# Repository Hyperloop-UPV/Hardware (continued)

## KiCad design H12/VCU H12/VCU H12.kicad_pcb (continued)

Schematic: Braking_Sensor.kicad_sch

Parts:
C108, C109, C110, C111, C112, C113: 0.1uF; CAP 0603_1608
C114: 1.6u; C_0603_1608Metric
C115: 0.1u; C_0603_1608Metric
IC7, IC12: SN74LVC86AD; SOIC127P600X175-14N; Manufacturer_Part_Number SN74LVC86AD; Mouser Part Number 595-SN74LVC86AD
IC8, IC9, IC10, IC11: SN74LVC08AD; SOIC127P600X175-14N; Manufacturer_Part_Number SN74LVC08AD; Mouser Part Number 595-SN74LVC08AD
IC13: SN74LVC1G17DBVR; Manufacturer_Part_Number SN74LVC1G17DBVR; Mouser Part Number 595-SN74LVC1G17DBVR
J27: 206832-0401; 206832-0401-Footprint-1; MAX VOLTAGE 600V AC (RMS)/DC
R150: 670; R_0603_1608Metric
R151, R152: 0 Ohms; RES 0603_1608; RATINGS AEC-Q200; TOLERANCE Jumper; PART NUMBER TLRZ1JTTD
TP42, TP43, TP44, TP45, TP46, TP47, TP48, TP49, TP50, TP51, TP52, TP53, TP54, TP55, TP56, TP57, TP58, TP59, TP60, TP61, TP62, TP63, TP64, TP65, TP66, TP67, TP68, TP69, TP70, TP71, TP72, TP73, TP74, TP75, TP77, TP78, TP79, TP80: Test point 1.2mm; Test point 1.2mm-Footprint-1

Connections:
+3V3: C108.1, C109.1, C110.1, C111.1, C112.1, C113.1, C115.1, IC7.14 (VCC), IC8.14 (VCC), IC9.14 (VCC), IC10.14 (VCC), IC11.14 (VCC), IC12.14 (VCC), IC13.5 (VCC); also elsewhere on the board
/Braking_Sensor/BRAKE_FAULT: IC11.12 (4A), IC13.4 (Y); also elsewhere on the board
/Braking_Sensor/BRAKE_RESET: IC9.9 (3A), R151.1, TP71.1 (*_1); also elsewhere on the board
/Braking_Sensor/GD_Reset_bypass: J27.3, J27.4, R151.2, R152.2, TP70.1 (*_1)
/Braking_Sensor/SENSOR_1_NC_OUT: IC7.2 (1B), TP43.1 (*_1); also elsewhere on the board
/Braking_Sensor/SENSOR_1_NO_OUT: IC7.1 (1A), IC10.1 (1A), TP42.1 (*_1); also elsewhere on the board
/Braking_Sensor/SENSOR_2_NC_OUT: IC7.5 (2B), TP47.1 (*_1); also elsewhere on the board
/Braking_Sensor/SENSOR_2_NO_OUT: IC7.4 (2A), IC10.2 (1B), TP46.1 (*_1); also elsewhere on the board
/Braking_Sensor/SENSOR_3_NC_OUT: IC7.10 (3B), TP49.1 (*_1); also elsewhere on the board
/Braking_Sensor/SENSOR_3_NO_OUT: IC7.9 (3A), IC10.4 (2A), TP48.1 (*_1); also elsewhere on the board
/Braking_Sensor/SENSOR_4_NC_OUT: IC7.13 (4B), TP54.1 (*_1); also elsewhere on the board
/Braking_Sensor/SENSOR_4_NO_OUT: IC7.12 (4A), IC10.5 (2B), TP53.1 (*_1); also elsewhere on the board
/Braking_Sensor/SENSOR_5_NC_OUT: IC12.2 (1B), TP57.1 (*_1); also elsewhere on the board
/Braking_Sensor/SENSOR_5_NO_OUT: IC10.9 (3A), IC12.1 (1A), TP55.1 (*_1); also elsewhere on the board
/Braking_Sensor/SENSOR_6_NC_OUT: IC12.5 (2B), TP62.1 (*_1); also elsewhere on the board
/Braking_Sensor/SENSOR_6_NO_OUT: IC10.10 (3B), IC12.4 (2A), TP59.1 (*_1); also elsewhere on the board
/Braking_Sensor/SENSOR_7_NC_OUT: IC12.10 (3B), TP66.1 (*_1); also elsewhere on the board
/Braking_Sensor/SENSOR_7_NO_OUT: IC10.12 (4A), IC12.9 (3A), TP64.1 (*_1); also elsewhere on the board
/Braking_Sensor/SENSOR_8_NC_OUT: IC12.13 (4B), TP69.1 (*_1); also elsewhere on the board
/Braking_Sensor/SENSOR_8_NO_OUT: IC10.13 (4B), IC12.12 (4A), TP67.1 (*_1); also elsewhere on the board
/MCU/RELEASED: IC9.10 (3B), IC11.11 (4Y), TP72.1 (*_1); also elsewhere on the board
GND: C108.2, C109.2, C110.2, C111.2, C112.2, C113.2, C114.2, C115.2, IC7.7 (GND), IC8.7 (GND), IC9.7 (GND), IC10.7 (GND), IC11.7 (GND), IC12.7 (GND), IC13.3 (GND), J27.1, J27.2; also elsewhere on the board
unnamed: IC7.3 (1Y), IC8.1 (1A), TP44.1 (*_1)
unnamed: IC7.6 (2Y), IC8.2 (1B), TP45.1 (*_1)
unnamed: IC7.8 (3Y), IC8.4 (2A), TP51.1 (*_1)
unnamed: IC7.11 (4Y), IC8.5 (2B), TP52.1 (*_1)
unnamed: IC8.3 (1Y), IC9.1 (1A)
unnamed: IC8.6 (2Y), IC9.2 (1B)
unnamed: IC8.8 (3Y), IC9.4 (2A), TP58.1 (*_1)
unnamed: IC8.11 (4Y), IC9.5 (2B), TP63.1 (*_1)
unnamed: IC9.3 (1Y), IC9.12 (4A), TP50.1 (*_1)
unnamed: IC9.6 (2Y), IC9.13 (4B), TP60.1 (*_1)
unnamed: IC9.8 (3Y), R152.1
unnamed: IC9.11 (4Y), R150.1
unnamed: IC10.3 (1Y), IC11.1 (1A), TP73.1 (*_1)
unnamed: IC10.6 (2Y), IC11.2 (1B), TP75.1 (*_1)
unnamed: IC10.8 (3Y), IC11.4 (2A), TP78.1 (*_1)
unnamed: IC10.11 (4Y), IC11.5 (2B), TP80.1 (*_1)
unnamed: IC11.3 (1Y), IC11.9 (3A), TP74.1 (*_1)
unnamed: IC11.6 (2Y), IC11.10 (3B), TP79.1 (*_1)
unnamed: IC11.8 (3Y), IC11.13 (4B), TP77.1 (*_1)
unnamed: IC8.9 (3A), IC12.3 (1Y), TP56.1 (*_1)
unnamed: IC8.10 (3B), IC12.6 (2Y), TP61.1 (*_1)
unnamed: IC8.12 (4A), IC12.8 (3Y), TP65.1 (*_1)
unnamed: IC8.13 (4B), IC12.11 (4Y), TP68.1 (*_1)
unnamed: C114.1, IC13.2 (A), R150.2

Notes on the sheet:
XOR
Limit switch logic
AND
When Brake Disengaged, RELEASED = 1
1ms delay
NEVER solder both 0 ohm resistors at the same time
If BRAKE_FAULT = 0 something goes wrong
We need 3V3 in the gate driver RESET pin to enable PWMs
Connector to PPU and LPU Gate Drivers
The RESET pin in the gate driver works like a ENABLE

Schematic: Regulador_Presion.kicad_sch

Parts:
C116: 0.1 µF; CAP 0603_1608; TOLERANCE ±10%; VOLTAGE - RATED 50V; PART NUMBER C0603X104K050T
C117: 1 µF; CAP 1206_3216 - 0.8MM; RATINGS AEC-Q200; TOLERANCE ±10%; PART NUMBER C1206C105K5RACAUTO
C118, C119: 0.1 µF; CAP 0603_1608; RATINGS AEC-Q200; TOLERANCE ±10%; PART NUMBER CGA3E2X7R1H104K080AE
F1: 0308.500UR; New footprint 1; CURRENT RATING 500mA
J28: 206832-0401; 206832-0401-Footprint-1; MAX VOLTAGE 600V AC (RMS)/DC
R153: 100 kOhms; RES 0603_1608; TOLERANCE ±1%; PART NUMBER CRCW0603100KFKEAC
R154: 0 Ohm; FP-CRG0603-IPC_C; VOLTAGE RATING 50V; POWER RATING 100mW
R155: 5.1kOhms; YAGEO RES 0603_1608; TOLERANCE ±1%; PART NUMBER RT0603FRE0710KL
R156: 10kOhms; YAGEO RES 0603_1608; TOLERANCE ±0.1%; PART NUMBER RT0603BRD074K7L
R157: 39 kOhms; YAGEO RES 0603_1608; TOLERANCE ±1%; PART NUMBER RT0603FRE0710KL
R158: 1kOhms; RESC1608X55X25LL10T15; PART NUMBER RC0603JR-101KL
R159: 68 kOhms; RES 0603_1608; RATINGS AEC-Q200; TOLERANCE ±1%; PART NUMBER RMCF0603FT6K80
T4, T5: Test point 1.2mm; Test point 1.2mm-Footprint-1
U11: MCP6022-E/SN; SOIC-SN8_N; VOLTAGE GAIN-MIN 31620; SUPPLY VOLTAGE-NOM (VSU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 5V

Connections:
+5V: C116.2, C117.1, U11.8 (VDD); also elsewhere on the board
/MCU/REGULATOR_IN: R153.1; also elsewhere on the board
/MCU/REGULATOR_OUT: C119.2, R158.2, T5.1 (*_1); also elsewhere on the board
/Regulador_Presion/3.18V: R157.1, R159.2, U11.5 (VINB+)
/Regulador_Presion/REG_IN: J28.4, R154.2, T4.1 (*_1)
/Regulador_Presion/REG_OUT: J28.3, R157.2
/Regulador_Presion/V_SUPPLY_1: F1.2, J28.1
GND: C116.1, C117.2, C118.1, C119.1, J28.2, R156.1, R159.1, U11.4 (VSS); also elsewhere on the board
unnamed: C118.2, R153.2, U11.3 (VINA+)
unnamed: R155.2, R156.2, U11.2 (VINA-)
unnamed: R154.1, R155.1, U11.1 (VOUTA)
unnamed: R158.1, U11.6 (VINB-), U11.7 (VOUTB)
VBAT: F1.1; also elsewhere on the board

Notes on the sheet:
Conector
Regulator OUT
Regulator IN
Supply
Resistencia de 0 Ohms para poder ajustar la resistencia interna del regulador. La Rinterna es de 250 ohms, a 5V max = 20mA.
Señal de 0V to 3.3V (0.005 to 0.9 MPa)
Gain de 1.51 (para pasar de 3.3V a 5V max)
1V to 5V (0.005 to 0.9MPa)
0.636V to 3.18V (0.005 to 0.9MPa)
Pin Out: Brown = Vdc (24V) Blue = GND White = Analog Signal IN, sink type (4mA to 20mA) Black = Analog Signal Monitoring (1V to 5V) Rango de presion (0.005 to 0.9 MPa)

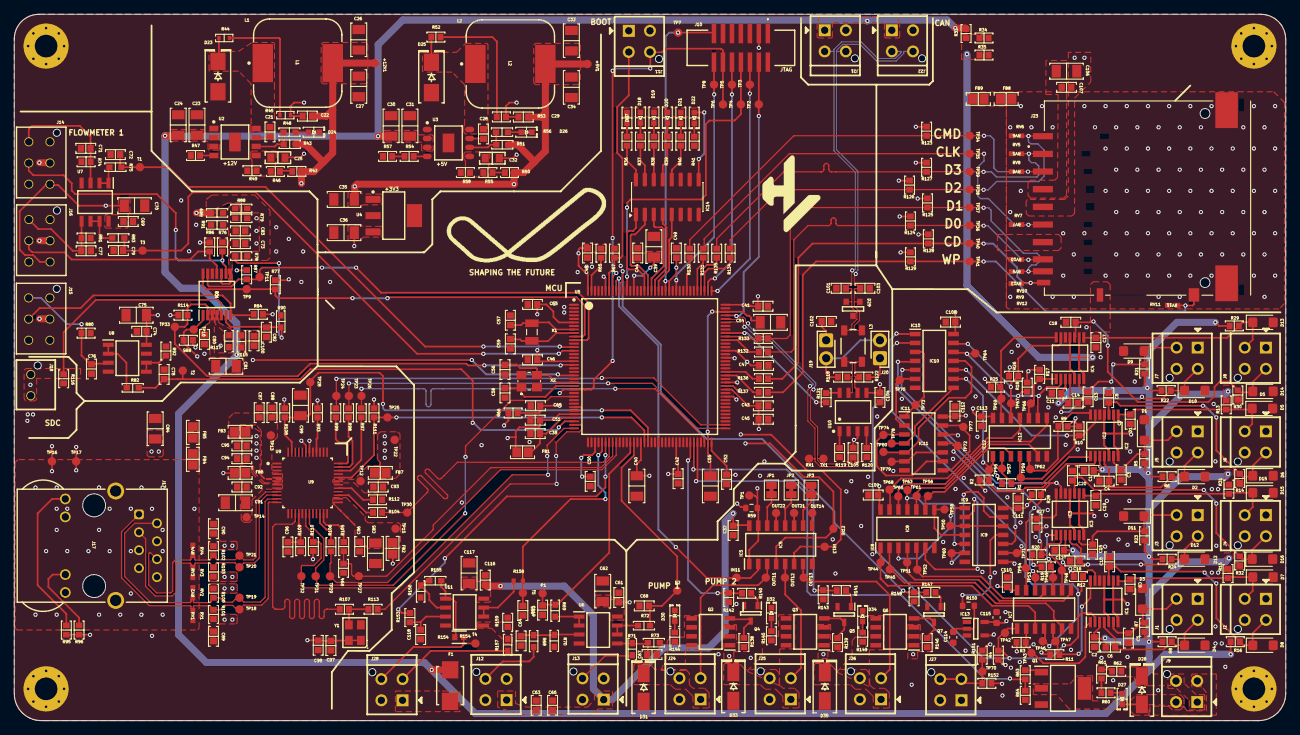
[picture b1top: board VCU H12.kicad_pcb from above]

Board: 6 copper layers, 180.0 x 100.0 mm, 506 parts (0 on the bottom side), 258 nets.

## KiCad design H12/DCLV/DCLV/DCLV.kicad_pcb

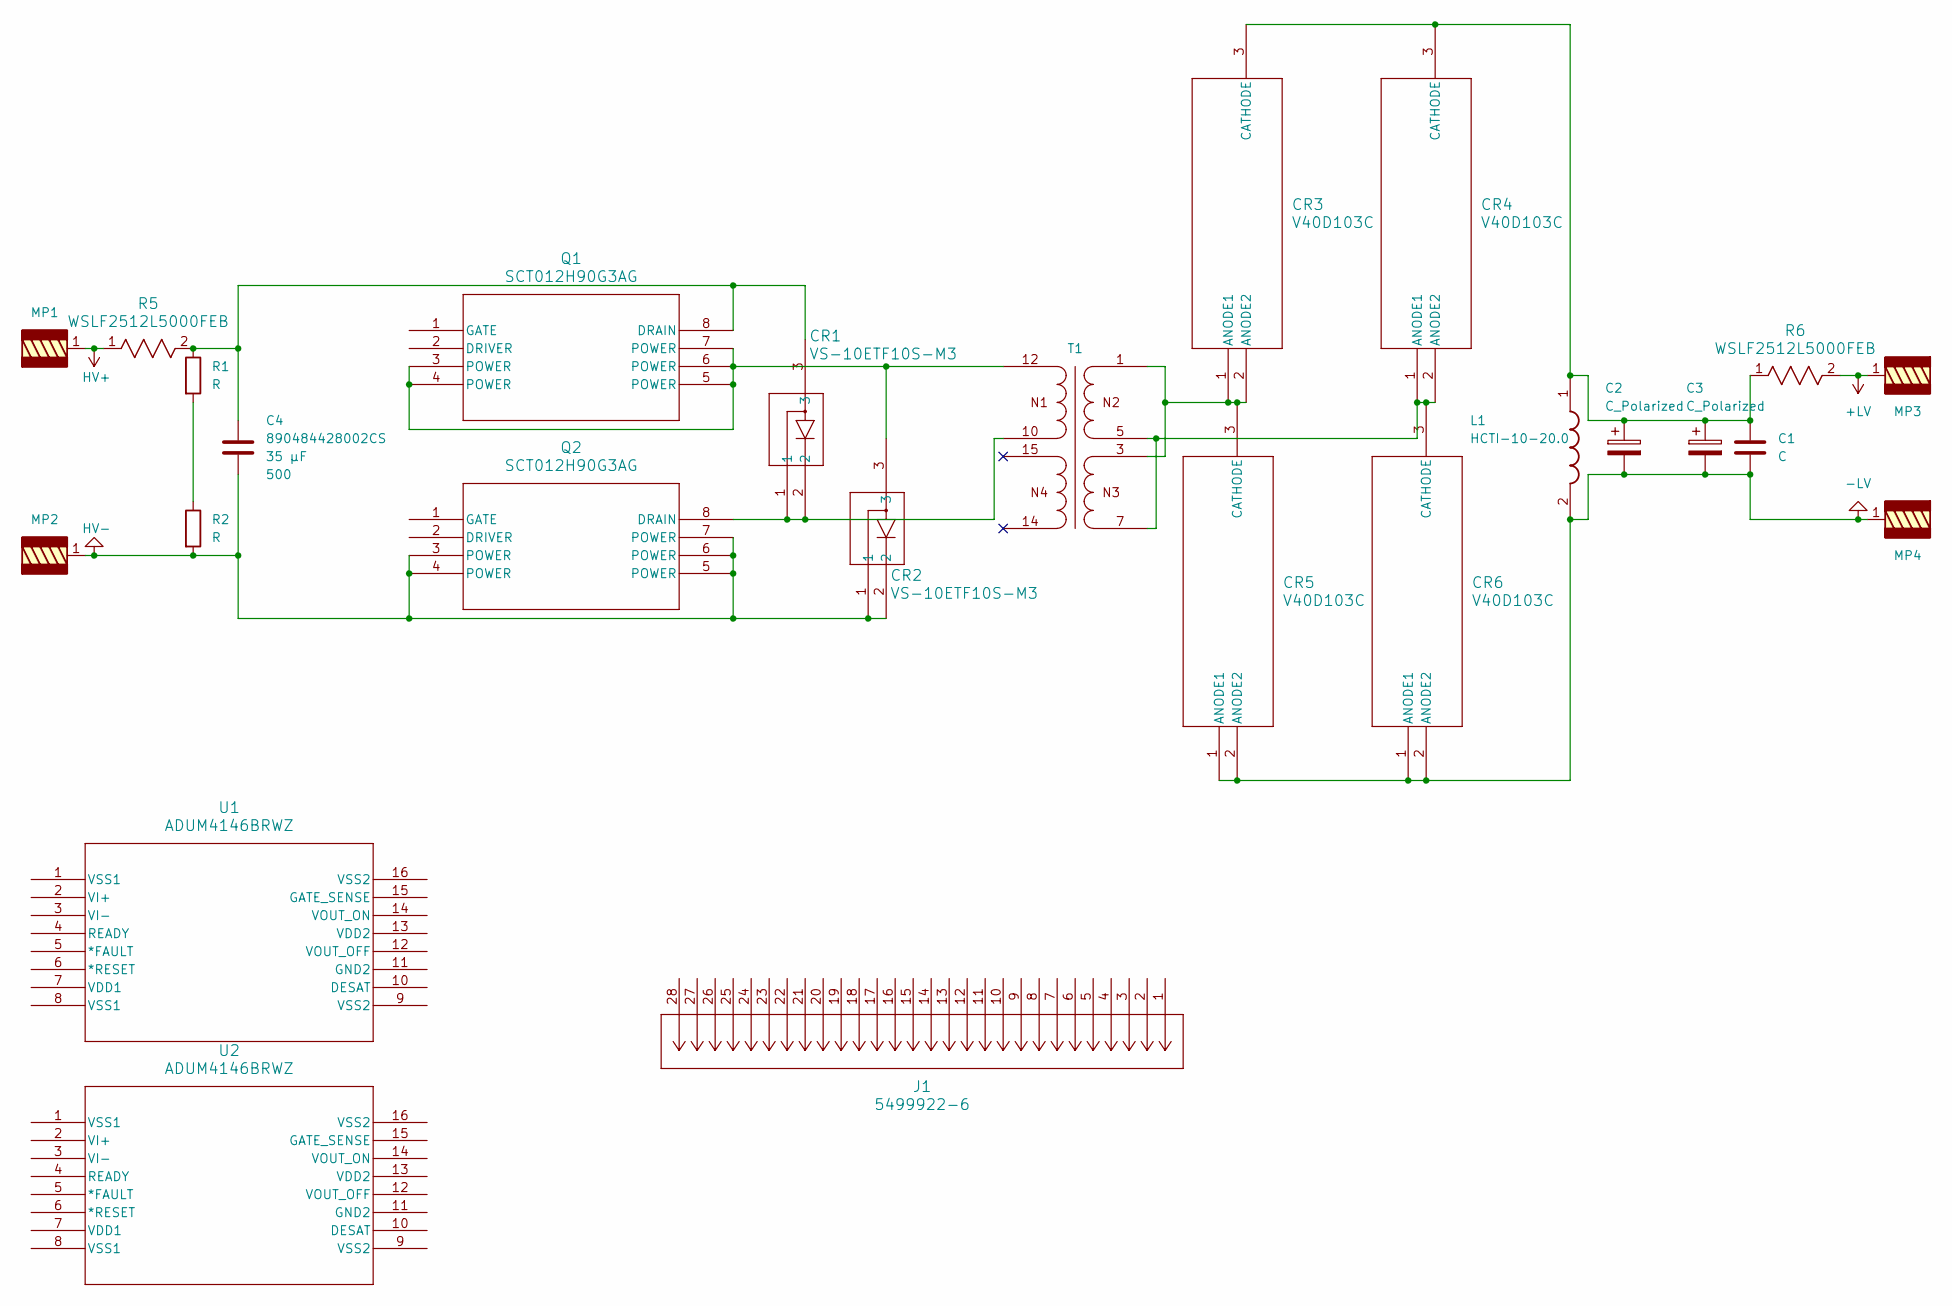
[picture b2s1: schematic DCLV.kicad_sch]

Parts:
C1: C; C_0805_2012Metric_Pad1.18x1.45mm_HandSolder
C2, C3: C_Polarized; CP_Radial_D18.0mm_P7.50mm
C4: L42W24H36_890484428002CS; C_Wurth_WCAP-FTDB-L42W24H36; Voltage 500; Part Number 890484428002CS
CR1, CR2: VS-10ETF10S-M3; TO-263AB_VIS
CR3, CR4, CR5, CR6: V40D103C; SDO_TO263AC_VIS
J1: 5499922-6; CON26_2X13_SHM_TEC
L1: HCTI-10-20.0; HCTI10200; Mouser Part Number 530-HCTI-10-20.0
MP1, MP2, MP3, MP4: 7460408; MP_Wurth_WP-BUCF_7460408; Part Number 7460408
Q1, Q2: SCT012H90G3AG; H2PAK-7_STM
R1, R2: R; R_1206_3216Metric_Pad1.30x1.75mm_HandSolder
R5, R6: WSLF2512L5000FEB; RES_WSLF2512_VIS
T1: ETD44_760895741; T_Wurth_WE-LLCR-ETD44; Part Number 760895741
U1, U2: ADUM4146BRWZ; RW-16_ADI

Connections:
HV+: MP1.1 (1_1), R5.1
HV-: C4.2, CR2.1, CR2.2, MP2.1 (1_1), Q2.3 (POWER), Q2.4 (POWER), Q2.5 (POWER), Q2.6 (POWER), Q2.7 (POWER), R2.2
LV+: MP3.1 (1_1), R6.2
LV-: C1.2, C2.2, C3.2, CR5.1 (ANODE1), CR5.2 (ANODE2), CR6.1 (ANODE1), CR6.2 (ANODE2), L1.2, MP4.1 (1_1)
unnamed: CR2.3, Q1.3 (POWER), Q1.4 (POWER), Q1.5 (POWER), Q1.6 (POWER), Q1.7 (POWER), T1.12
unnamed: CR3.1 (ANODE1), CR3.2 (ANODE2), CR5.3 (CATHODE), T1.1, T1.2, T1.3, T1.4
unnamed: C1.1, C2.1, C3.1, CR3.3 (CATHODE), CR4.3 (CATHODE), L1.1, R6.1
unnamed: CR4.1 (ANODE1), CR4.2 (ANODE2), CR6.3 (CATHODE), T1.5, T1.6, T1.7, T1.8
unnamed: C4.1, CR1.3, Q1.8 (DRAIN), R1.1, R5.2
unnamed: CR1.1, CR1.2, Q2.8 (DRAIN), T1.10
unnamed: R1.2, R2.1

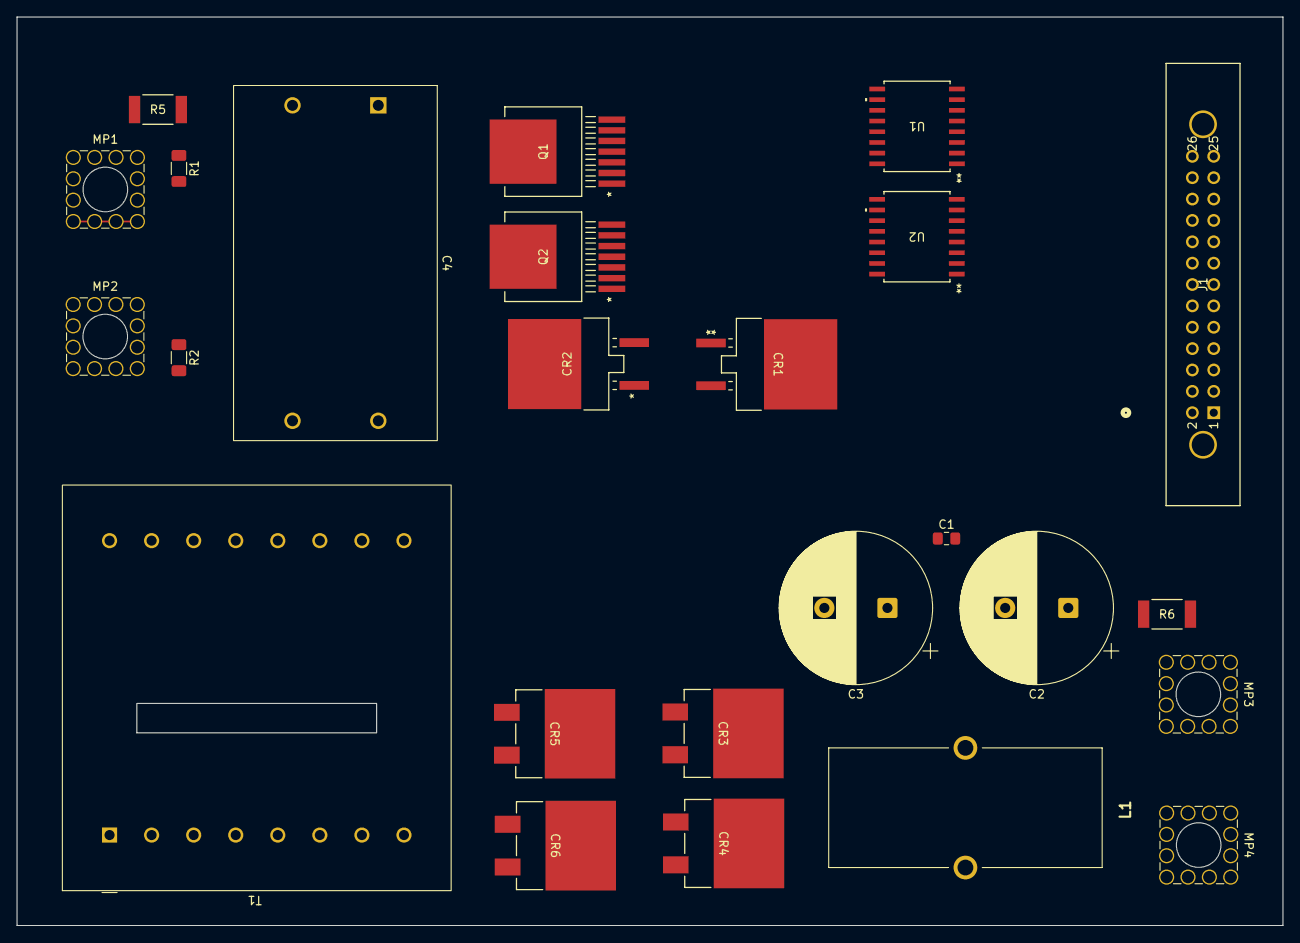
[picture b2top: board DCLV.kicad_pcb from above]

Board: 4 copper layers, 150.5 x 108.0 mm, 25 parts (0 on the bottom side), 11 nets.

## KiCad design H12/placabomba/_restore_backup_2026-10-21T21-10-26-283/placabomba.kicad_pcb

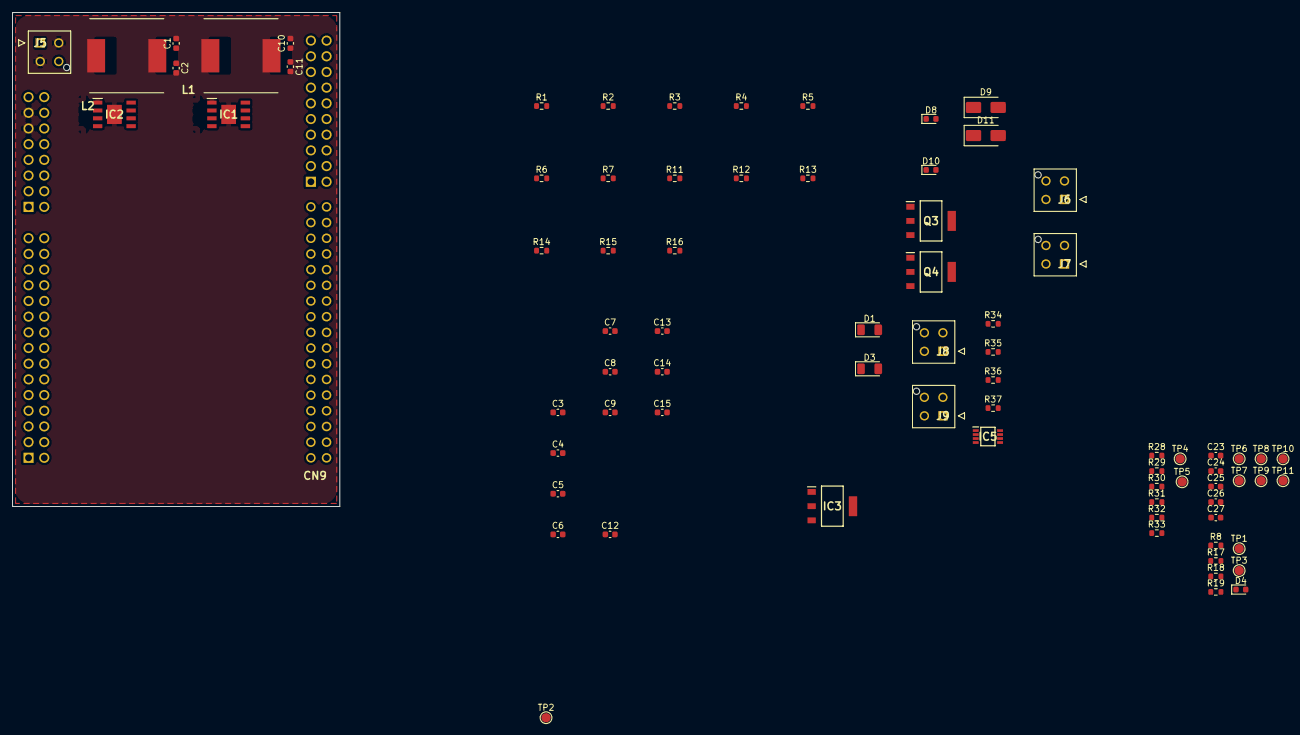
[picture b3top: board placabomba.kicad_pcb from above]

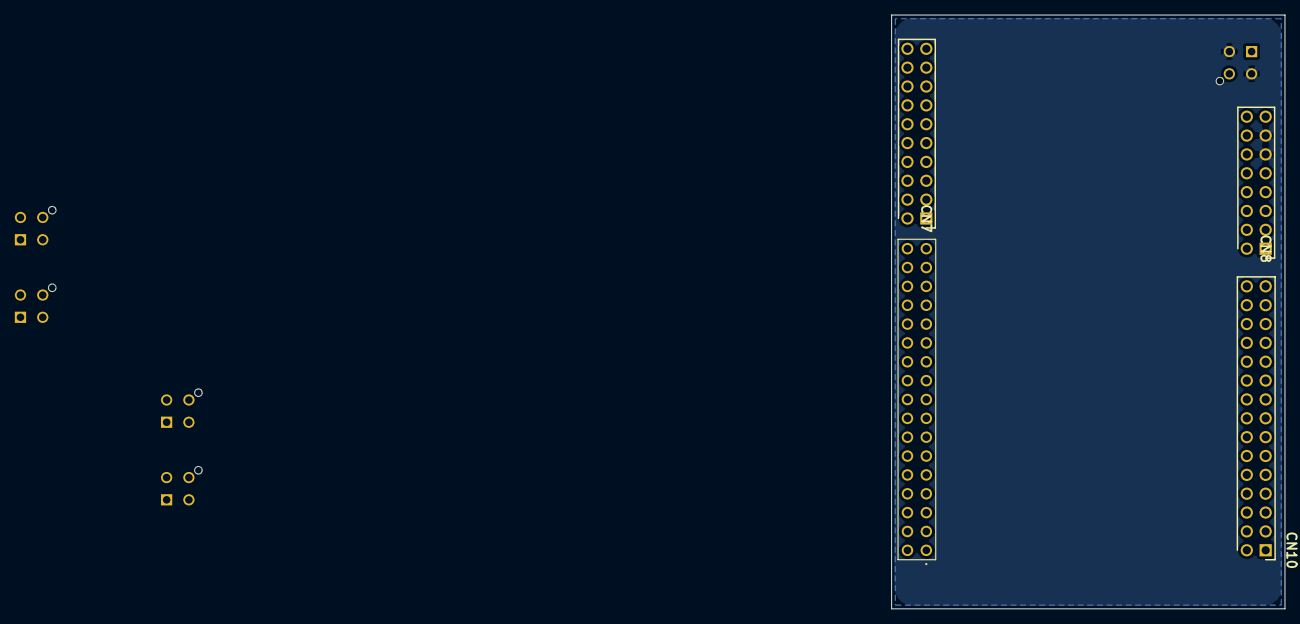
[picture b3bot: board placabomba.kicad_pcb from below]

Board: 2 copper layers, 53.0 x 80.0 mm, 82 parts (4 on the bottom side), 39 nets, no tracks yet.

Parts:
C1, C2, C10, C11: 2.2uF; C_0603_1608Metric
C3, C12, C23, C26, C27: 0.1uF; C_0603_1608Metric
C4: 56pF; C_0603_1608Metric
C5: 2200pF; C_0603_1608Metric
C6, C7, C15: 22uF; C_0603_1608Metric
C8, C9: 10uF; C_0603_1608Metric
C13: 47pF; C_0603_1608Metric
C14: 1200pF; C_0603_1608Metric
C24, C25: 100uF; C_0603_1608Metric
CN7: TSW-110-23-G-D; HDRV20W64P254_2X10_2540X495X838P
CN8: TSW-108-23-G-D; HDRV16W64P254_2X8_2032X495X838P
CN9: TSW-115-23-G-D; TSW-117-XX-YY-D
CN10: TSW-117-07-G-D; HDRV30W64P254_2X15_3810X508X838P
D1, D3: SK510BH-LTP; D_1206_3216Metric
D4, D8, D10: LED; LED_0603_1608Metric
D9, D11: SS36; D_SMA
IC1, IC2: LM5013QDDARQ1; SOIC127P600X170-9N
IC3: LT1963AEST-3.3#TRPBF; SOT230P700X180-4N
IC5: 74AHCT2G125DP-Q10H; SOP65P400X110-8N
J5, J6, J7, J8, J9: 2068320401; 20683204YY
L1, L2: 744771112
Q3, Q4: BUK9875-100A_CUX; SOT230P700X180-4N
R1: 39k; R_0603_1608Metric
R2, R12: 2.2k; R_0603_1608Metric
R3: 180k; R_0603_1608Metric
R4: 68k; R_0603_1608Metric
R5: 270k; R_0603_1608Metric
R6: 56k; R_0603_1608Metric
R7, R11, R16: 100k; R_0603_1608Metric
R8: 2.7k; R_0603_1608Metric
R13: 330k; R_0603_1608Metric
R14: 220k; R_0603_1608Metric
R15: 680k; R_0603_1608Metric
R17, R19: 10; R_0603_1608Metric
R18: 10k; R_0603_1608Metric
R28, R31: 10K; R_0603_1608Metric
R29, R32, R35, R36: 330; R_0603_1608Metric
R30, R33: 1.5K; R_0603_1608Metric
R34, R37: 4.7k; R_0603_1608Metric
TP1: +5V; TestPoint_Pad_D1.5mm
TP2: +3V3; TestPoint_Pad_D1.5mm
TP3: +12V; TestPoint_Pad_D1.5mm
TP4: POWER1; TestPoint_Pad_D1.5mm
TP5: POWER2; TestPoint_Pad_D1.5mm
TP6: TACHO1; TestPoint_Pad_D1.5mm
TP7: CONTROL1_IN; TestPoint_Pad_D1.5mm
TP8: CONTROL2_IN; TestPoint_Pad_D1.5mm
TP9: TACHO2; TestPoint_Pad_D1.5mm
TP10: LED1; TestPoint_Pad_D1.5mm
TP11: LED2; TestPoint_Pad_D1.5mm

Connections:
+3V3: C9.1, IC3.3 (OUT), R34.1, R37.1, TP2.1 (1_1)
+5V: C5.1, C6.1, C7.1, C8.1, C23.1, C24.1, C25.1, C26.1, C27.1, IC3.1 (IN), IC5.8 (VCC), J8.4, J9.4, L1.2, R6.2, TP1.1 (1_1)
+12V: C14.1, C15.1, D9.1 (K), D11.1 (K), L2.2, R14.2, R30.1, R33.1, TP3.1 (1_1)
+24V: C1.1, C2.1, C10.1, C11.1, IC1.2 (VIN), IC1.3 (EN/UVLO), IC2.2 (VIN), IC2.3 (EN/UVLO), J5.1, J5.4
/Buckconverter/FB_5V: C4.1, IC1.5 (FB), R5.1, R7.2
/Buckconverter/FB_12V: C13.1, IC2.5 (FB), R15.1, R16.2
/Buckconverter/PGOOD_5V: IC1.6 (PGOOD), R8.2, R17.1
/Buckconverter/PGOOD_12V: IC2.6 (PGOOD), R18.2, R19.1
/bombacontrol/CONTROL1: CN7.16, J6.4, TP7.1 (1_1)
/bombacontrol/CONTROL2: CN7.14, J7.4, TP8.1 (1_1)
/bombacontrol/TACHO1: CN7.18, J6.3, R34.2, TP6.1 (1_1)
/bombacontrol/TACHO2: J7.3, R37.2, TP9.1 (1_1)
/bombapower/POWER1: D8.1 (K), D9.2 (A), J6.1, Q3.2 (D_1), Q3.4 (D_2), TP4.1 (1_1)
/bombapower/POWER1_CONTROL: CN10.4, R28.1, R29.1
/bombapower/POWER2: D10.1 (K), D11.2 (A), J7.1, Q4.2 (D_1), Q4.4 (D_2), TP5.1 (1_1)
/bombapower/POWER2_CONTROL: CN10.6, R31.1, R32.1
GND: C1.2, C2.2, C6.2, C7.2, C8.2, C9.2, C10.2, C11.2, C15.2, C23.2, C24.2, C25.2, C26.2, C27.2, CN8.11, CN8.13, D1.2 (A), D3.2 (A), D4.1 (K), IC1.1 (GND), IC1.9 (EP), IC2.1 (GND), IC2.9 (EP), IC3.2 (GND_1), IC3.4 (GND_2), IC5.1 (~1OE), IC5.4 (GND), IC5.7 (~2OE), J5.2, J5.3, J6.2, J7.2, J8.3, J9.3, Q3.3 (S), Q4.3 (S), R2.2, R7.1, R11.2, R16.1, R19.2, R28.2, R31.2
unnamed: C4.2, C5.2, R4.2
unnamed: C13.2, C14.2, R13.2
unnamed: C3.2, D1.1 (K), IC1.8 (SW), L1.1, R3.1, R8.1
unnamed: C12.2, D3.1 (K), IC2.8 (SW), L2.1, R12.1, R18.1
unnamed: D4.2 (A), R17.2
unnamed: D8.2 (A), R30.2
unnamed: D10.2 (A), R33.2
unnamed: C3.1, IC1.7 (BST)
unnamed: IC1.4 (RON), R1.1
unnamed: C12.1, IC2.7 (BST)
unnamed: IC2.4 (RON), R11.1
unnamed: IC5.6 (1Y), R35.1
unnamed: IC5.3 (2Y), R36.1
unnamed: J8.2, R35.2, TP10.1 (1_1)
unnamed: J9.2, R36.2, TP11.1 (1_1)
unnamed: Q3.1 (G), R29.2
unnamed: Q4.1 (G), R32.2
unnamed: R1.2, R2.1
unnamed: R3.2, R4.1
unnamed: R5.2, R6.1
unnamed: R12.2, R13.1
unnamed: R14.1, R15.2

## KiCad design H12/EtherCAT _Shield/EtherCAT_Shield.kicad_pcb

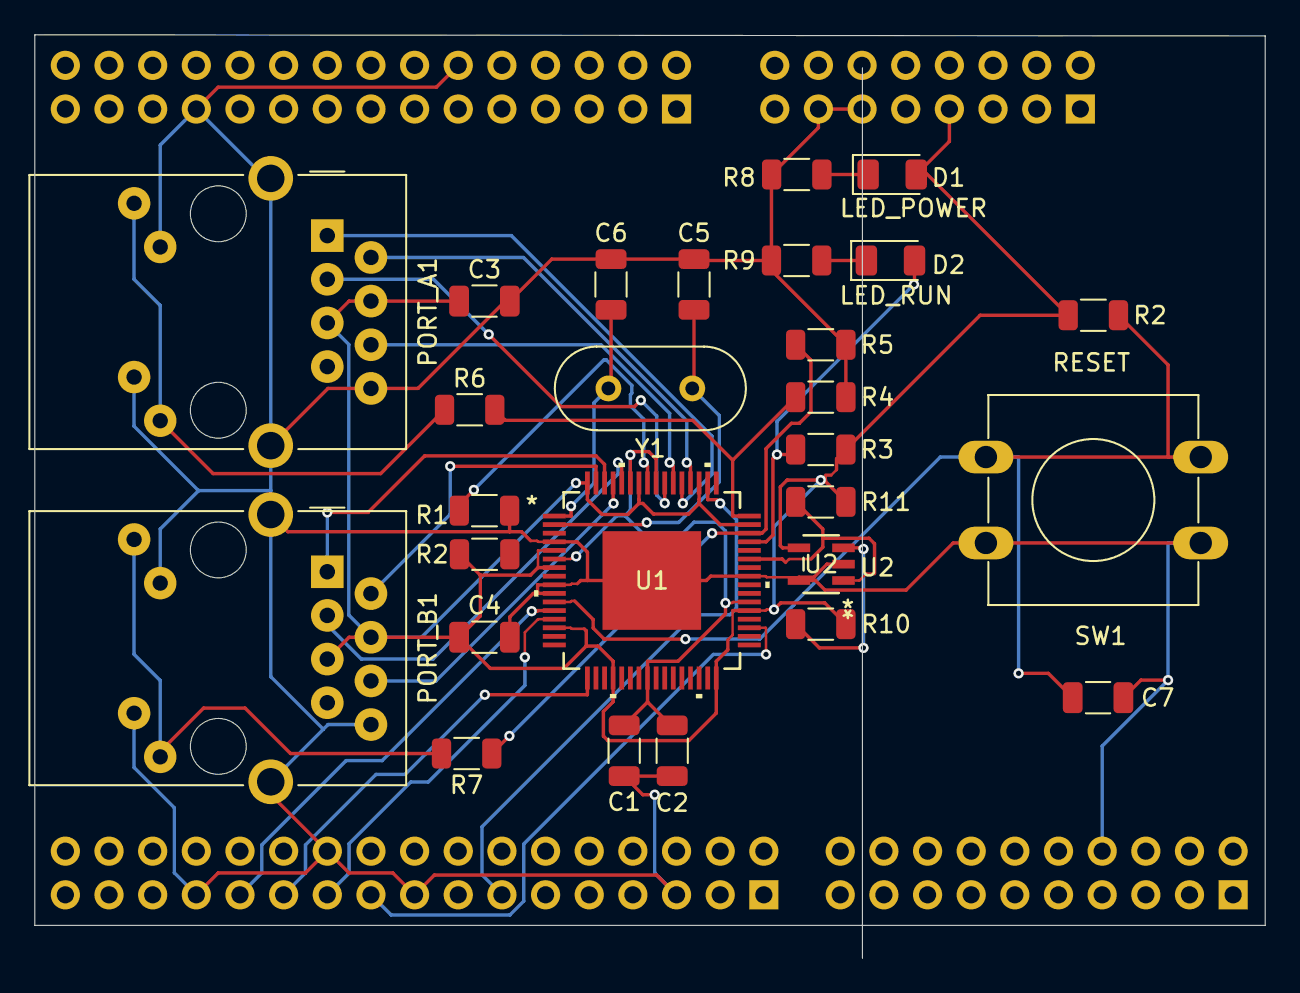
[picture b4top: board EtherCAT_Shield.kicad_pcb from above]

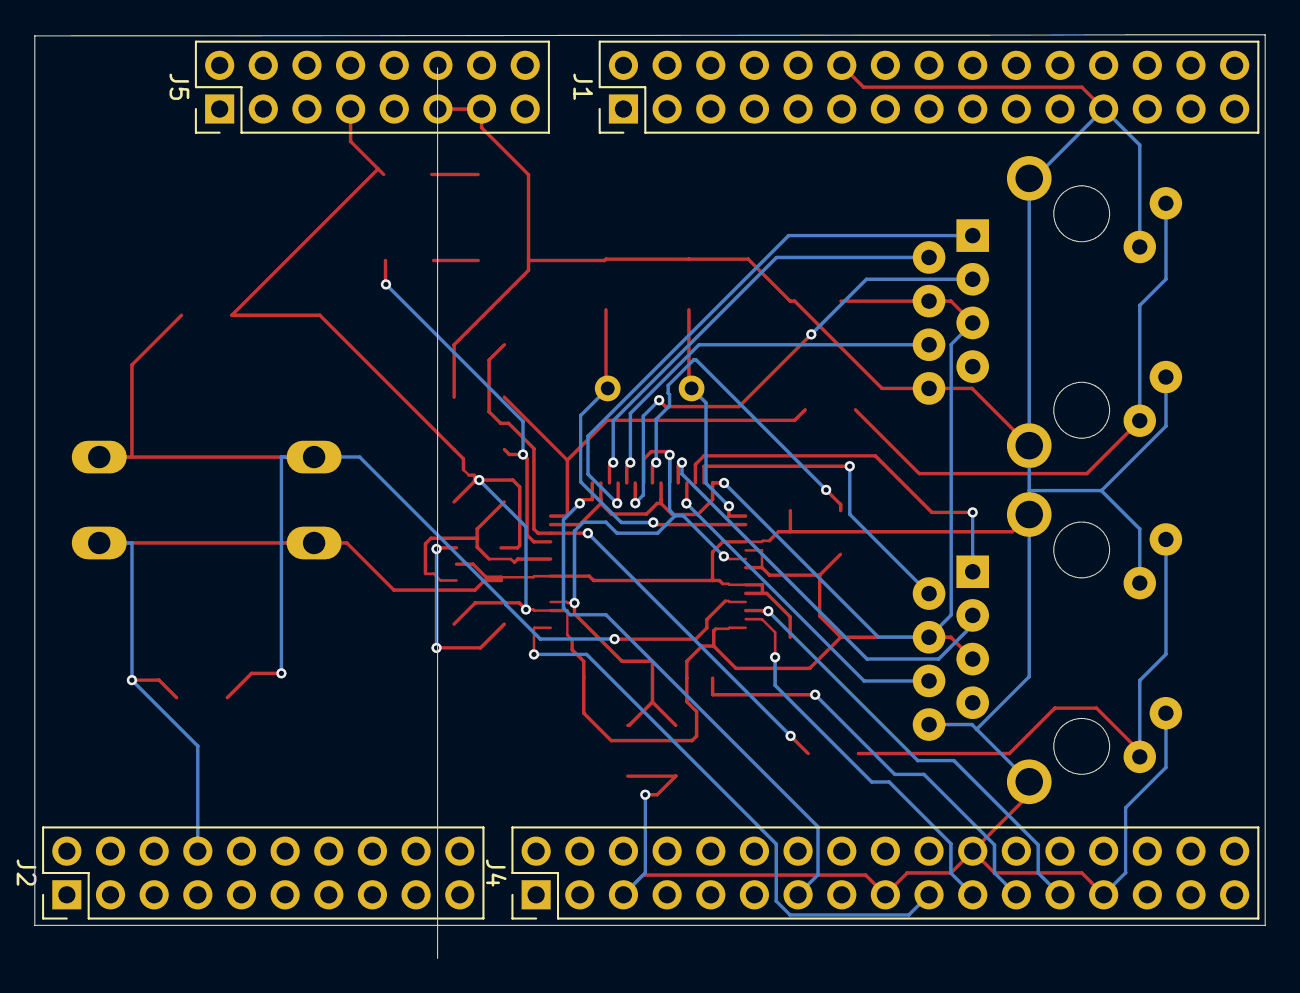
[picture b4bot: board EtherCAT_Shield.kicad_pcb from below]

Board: 2 copper layers, 71.6 x 53.7 mm, 31 parts (4 on the bottom side), 29 nets.

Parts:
C1: 1uF; C_1206_3216Metric
C2: 470pF; C_1206_3216Metric
C3, C4: 22nF; C_1206_3216Metric
C5, C6: 30pF; C_1206_3216Metric
C7: 100nF; C_1206_3216Metric
D1: LED_POWER; LED_1206_3216Metric
D2: LED_RUN; LED_1206_3216Metric
J1: Conn_02x15_Odd_Even; PinHeader_2x15_P2.54mm_Vertical
J2: Conn_02x10_Odd_Even; PinHeader_2x10_P2.54mm_Vertical
J4: Conn_02x17_Odd_Even; PinHeader_2x17_P2.54mm_Vertical
J5: Conn_02x08_Odd_Even; PinHeader_2x08_P2.54mm_Vertical
PORT_A1: RJ45_Amphenol_RJMG1BD3B8K1ANR
PORT_B1: RJ45_Amphenol_RJMG1BD3B8K1ANR
R1: 12.1K 1%; R_1206_3216Metric
R2, R2#2: 1K; R_1206_3216Metric
R3, R4, R5, R10, R11: 4.7K; R_1206_3216Metric
R6, R7, R8, R9: 330; R_1206_3216Metric
SW1: RESET; SW_PUSH-12mm
U1: LAN9252I/PT; TQFP-EP64_PT_MCH
U2: 24AA64T-E/OT; SOT-23-5_MC_MCH
Y1: Crystal; Crystal_HC49-U_Vertical

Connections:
+3.3V: C3.1, C4.1, D1.2 (A), J5.7, PORT_A1.R4 (TCT), PORT_A1.R5 (RCT), PORT_B1.R4 (TCT), PORT_B1.R5 (RCT), R2.1, R2#2.1, R3.1, R10.2, R11.2, U1.5 (VDD33), U1.7 (REG_EN), U1.14 (VDDIO), U1.20 (VDDIO), U1.32 (VDDIO), U1.37 (VDDIO), U1.47 (VDDIO), U1.51 (VDD33TXRX1), U1.58 (VDD33BIAS), U1.64 (VDD33TXRX2), U2.4 (VCC)
/ACTLED0: R4.1, R6.2, U1.48 (LINKACTLED0/TDO/CHIP_MODE0)
/ACTLED1: R5.1, R7.1, U1.46 (LINKACTLED1/TDI/CHIP_MODE1)
/EEPROM_SCL: R11.1, U1.43 (EESCL/TCK), U2.1 (SCL)
/EEPROM_SDA: R10.1, U1.42 (EESDA/TMS), U2.3 (SDA)
/OSCI: C6.2, U1.1 (OSCI), Y1.1
/OSCO: C5.2, U1.2 (OSCO), Y1.2
/RST: C7.2, R2#2.2, SW1.2 (B), U1.11 (RST#)
/RUNLED: D2.2 (A), R3.2, U1.45 (RUNLED/E2PSIZE)
/SQI_CS: J4.13, U1.50 (D5/AD5/OUTVALID/SCS#)
/SQI_D0: J4.23, U1.17 (D0/AD0/WD_STATE/SI/SIO0)
/SQI_D1: J4.21, U1.13 (D1/AD1/EOF/SO/SIO1)
/SQI_D2: J4.25, U1.12 (D2/AD2/SOF/SIO2)
/SQI_D3: J4.19, U1.35 (D3/AD3/WD_TRIG/SIO3)
GND: C1.2, C2.2, C3.2, C4.2, C5.1, C6.1, C7.1, J1.12, J1.23, J2.8 (Pin_8_8), J4.5, J4.17, J4.22, J4.27, J5.11, J5.13, PORT_A1.L2, PORT_A1.L3, PORT_A1.R8, PORT_A1.SH, PORT_B1.L2, PORT_B1.L3, PORT_B1.R8, PORT_B1.SH, R1.1, R4.2, R5.2, R8.1, R9.1, SW1.1 (A), U1.4 (OSCVSS), U1.9 (FXSDA/FXLOSA/FXSDENA), U1.10 (FXSDB/FXLOSB/FXSDENB), U1.41 (TESTMODE), U1.EPAD (VSS), U2.2 (VSS), U2.5 (WP)
unnamed: D1.1 (K), R8.2
unnamed: D2.1 (K), R9.2
unnamed: PORT_A1.L1, PORT_A1.L4, R6.1
unnamed: PORT_A1.R3 (RD+), U1.55 (RXPA)
unnamed: PORT_A1.R6 (RD-), U1.54 (RXNA)
unnamed: PORT_A1.R1 (TD+), U1.53 (TXPA)
unnamed: PORT_A1.R2 (TD-), U1.52 (TXNA)
unnamed: PORT_B1.L1, PORT_B1.L4, R7.2
unnamed: PORT_B1.R3 (RD+), U1.60 (RXPB)
unnamed: PORT_B1.R6 (RD-), U1.61 (RXNB)
unnamed: PORT_B1.R1 (TD+), U1.62 (TXPB)
unnamed: PORT_B1.R2 (TD-), U1.63 (TXNB)
unnamed: R1.2, U1.57 (RBIAS)
unnamed: C1.1, C2.1, U1.6 (VDDCR), U1.24 (VDDCR), U1.38 (VDDCR), U1.56 (VDD12TX1), U1.59 (VDD12TX2)
